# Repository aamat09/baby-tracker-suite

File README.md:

# Baby Tracker Suite

A baby care tracking system built on Home Assistant, n8n, PostgreSQL, and ESP32. Born out of a contraction tracker built for labor, evolved into a full newborn care dashboard once my son arrived plus a ~$10 3D-printed physical remote for those 3am diaper-change logs.

## Features

- **One-tap logging** of feeds, diapers, sleep, baths, medicine, tummy time, weight, pumping, and notes. 17 event types across 8 categories
- **Multi-channel fan-out** on every press: PostgreSQL, both phones, Echo Show, and Discord via a single n8n webhook
- **Live HA dashboard** with daily stats (feeds/diapers today, sleep total, last feed/diaper) polled every 30s
- **3D-printed physical remote** ESP32-C3 + a 15-button 4x4 matrix + WS2812 feedback LED, MQTT over WiFi
- **Reproducible PCB**  fully-routed 2-layer KiCad board *and* a 3D-printed copper-tape groove board, both generated from script
- **2-hour pump reminders** with independent per-side timers
- **Retired contraction tracker**  the labor-day origin story, Ring panic button + on-demand Ollama labor-stage AI assessment

## The Story

When my wife went into labor, we needed a way to log contractions without fumbling with phone apps. We paired a Ring Alarm Panic Button (Z-Wave) to our home automation stack where one press logged the contraction, timestamped it in PostgreSQL, notified both phones, posted to Discord, and announced it on the Echo Show. It worked beautifully for 700+ contractions over two weeks.

When we got to the hospital, the Ring button was back home. So we added intensity-coded buttons (Mild/Moderate/Strong/Intense) to the HA dashboard with color coding, stats (average gap, frequency), and an on-demand AI assessment powered by Ollama that would estimate the labor stage.

My son was born the next day. The contraction tracker was retired the same day and replaced with a baby tracker covering feeds, diapers, sleep, baths, medicine, tummy time, weight, pumping, and notes.

Keeping the same low-friction (high-WAF) style, we then built a 3D-printed physical remote with labeled buttons so nobody has to unlock a phone to log a diaper change at 3am.

## Architecture

```
Physical Button / HA App / Siri Shortcut
        |
        v
   n8n Webhook (POST /webhook/baby-event)
        |
   +----+----+----+----+
   |    |    |    |    |
   v    v    v    v    v
  DB  Phone Phone Echo Discord
  PG   you   ptnr Show
        |
        v
   n8n Log API (GET /webhook/baby-log)
        |
        v
   HA REST Sensor (polls every 30s)
        |
        v
   HA Dashboard (stats + journal + buttons)
```

## Components

### Contraction Tracker (retired)

The original. Ring Panic Button press -> Z-Wave JS UI -> Python bridge -> MQTT + n8n webhook -> full pipeline.

| File | Description |
|------|-------------|
| `contraction-tracker/zwave_panic_mqtt.py` | Python bridge: Z-Wave WebSocket -> MQTT + webhook |
| `contraction-tracker/n8n/contraction_tracker.json` | Main workflow: webhook -> Discord, DB, notifications |
| `contraction-tracker/n8n/contraction_note_logger.json` | MQTT-triggered note logger |
| `contraction-tracker/n8n/contraction_log_api.json` | GET API: returns entries + 2-hour stats |
| `contraction-tracker/n8n/contraction_ai_assessment.json` | On-demand Ollama AI labor stage assessment |
| `contraction-tracker/ha/dashboard.json` | HA Lovelace dashboard (intensity buttons, journal, AI) |
| `contraction-tracker/ha/configuration_snippets.yaml` | HA config: rest_command, input_text, REST sensor |

Features added during labor:
- 4 color-coded intensity buttons (Mild/Moderate/Strong/Intense)
- Real-time stats: contraction count, average gap, average intensity (last 2 hours)
- On-demand AI assessment via Ollama (gpt-oss model) with timestamp
- Press feedback: haptic vibration + button scale animation
- iPhone home screen shortcut via Apple Shortcuts deep link

### Baby Tracker (active)

Full newborn care tracker. 17 event types across 8 categories.

| File | Description |
|------|-------------|
| `baby-tracker/n8n/baby_event_logger.json` | Main workflow: webhook -> DB + phone notifications |
| `baby-tracker/n8n/baby_note_logger.json` | MQTT-triggered note logger |
| `baby-tracker/n8n/baby_log_api.json` | GET API: returns entries + daily stats |
| `baby-tracker/n8n/pump_reminder.json` | 2-hour pump reminder (independent timers per pump) |
| `baby-tracker/ha/dashboard.json` | HA Lovelace dashboard |
| `baby-tracker/ha/configuration_snippets.yaml` | HA config snippets |

Event types:
- **Feed:** breast, bottle, solid
- **Pump:** left, right (with 2h reminder)
- **Diaper:** pee, poop, both, change
- **Other:** sleep (toggle), bath, medicine, tummy_time, weight
- **Notes:** regular, special (star-prefixed)

Stats tracked: last feed time/type, last diaper time/type, feeds today, diapers today, sleep total today, baths/medicines/tummy times/pumps today.

### Baby Tracker App — Home Assistant add-on (separate repo)

A **single-container Home Assistant app** that bundles everything above with
**no n8n and no external database**: an Ingress web UI (the colorful button
dashboard), local SQLite storage, the same stats/journal, pump reminders, and
native HA entities via MQTT discovery — and it still listens to the ESP32
remote. It lives in its own installable repo:

➡️ **[hms-homelab/hms-baby-tracker](https://github.com/hms-homelab/hms-baby-tracker)**
(FastAPI + SQLite; add the repo URL under Settings → Add-ons/Apps → Repositories).

<p align="center"><em>The add-on's Ingress web UI (left) and its Home Assistant app page (right) — runs as a native HA add-on, no n8n or external DB.</em></p>

The n8n + PostgreSQL path in this repo remains as the advanced/legacy backend;
the app is the portable, one-click way to run the whole thing.

### Baby Remote (in progress)

3D-printed physical remote control with ESP32-C3, 15 tactile buttons, RGB LED feedback, and a 0.96" OLED status screen.

<p align="center"><em>The remote with its 0.96" OLED — last feed, last pump and the next-pump reminder, pushed live over MQTT by n8n.</em></p>

> **🎛️ Want one without building it?** The remote is made in small batches —
> **[join the device waitlist →](https://www.shmaestro.com/waitlist)**.

| File | Description |
|------|-------------|
| `baby-remote/kicad/` | 2-layer PCB (DRC-clean, Freerouting-routed) — the manufactured board |
| `baby-remote/kicad/fab/baby-remote-jlcpcb.zip` | Gerbers + drill, ready to upload to JLCPCB |
| `baby-remote/scad/baby-remote-pcb.scad` | OpenSCAD 3D-printed PCB substrate (grooved board = device back; bottom feet) |
| `baby-remote/scad/baby-remote-pcb-case.scad` | OpenSCAD snap-fit cap (walls + ledge + barrels + labels); board snaps in |
| `baby-remote/scad/button_plunger.stl` | Button plunger (print 15×) |
| `baby-remote/scad/led_window.stl` | LED window (print 1× in clear filament) |
| `baby-remote/esphome/baby_remote.yaml` | ESPHome firmware: matrix -> MQTT -> n8n / the app |

See [Hardware](#hardware) for the button layout, matrix wiring, PCB, and BOM.

### Database

| File | Description |
|------|-------------|
| `db/schema.sql` | PostgreSQL schema for both tables |

Both tables live in the `maestro_hub` database on PostgreSQL 17 at homelab.local.

## Hardware

The **Baby Remote** is a 3D-printed, battery-powered ESP32-C3 keypad. 15 tactile
switches on a diodeless **4x4 scan matrix** (16th cell is the LED window), each
press published over MQTT to the same n8n webhook the app and Siri use.

Button layout (4x4 grid, last cell = RGB LED):
```
 Breast  | Bottle  |  Solid  |  Sleep
 Pump L  | Pump R  |  Bath   |  Meds
  Pee    |  Poop   |  Both   | Change
 Tummy   | Weight  |  Note   |  [LED]
```

Matrix -> GPIO (firmware `baby-remote/esphome/baby_remote.yaml` == PCB):

| Signal | GPIO | Net |
|---|---|---|
| Rows (drive) | GPIO0, GPIO1, GPIO3, GPIO4 | `ROW0..3` |
| Columns (sense) | GPIO5, GPIO6, GPIO7, GPIO10 | `COL0..3` |
| WS2812B LED | GPIO8 | `LED_DIN` |

PCB -- two interchangeable designs, both script-generated and reproducible:
- **KiCad** (`baby-remote/kicad/`)  fully-routed **2-layer** board (rows on
  F.Cu, columns on B.Cu), DRC clean (0 violations / 0 unconnected / 0 parity),
  Freerouting-routed, JLCPCB-ready. Regenerate with `gen_schematic.py` ->
  `pcbgen.py`; route via Specctra DSN/SES.
- **OpenSCAD groove board** (`baby-remote/scad/baby-remote-pcb.scad`)  3D-printed
  substrate with copper-tape/tinned-wire grooves; rows on the top face, columns
  on the bottom, switch legs bridging faces (crossing-free).

BOM (~$10):

| Part | Qty |
|---|---|
| ESP32-C3 SuperMini | 1 |
| TP4056 USB-C LiPo charger | 1 |
| 3.7V LiPo 500mAh | 1 |
| 6x6x5mm tactile switches | 15 |
| WS2812B RGB LED | 1 |
| Slide switch (power) | 1 |

## Infrastructure

- **Home Assistant:** KVM/VM at homeassistant.local (dashboards, scripts, REST sensors)
- **n8n:** Native at homelab.local:5678 (workflow automation, webhooks)
- **PostgreSQL 17:** Native at homelab.local:5432 (data storage)
- **EMQX:** Native at homelab.local:1883 (MQTT broker)
- **Ollama:** ollama.local:11434 (AI assessment, RTX 3050)
- **ESPHome:** For ESP32 device firmware

## Install as a Home Assistant App

The fastest path — no n8n, no PostgreSQL, no manual scripts:

1. **Settings → Add-ons → Add-on Store** (shown as **Apps** on HA 2026.2+) →
   ⋮ → **Repositories** → add `https://github.com/hms-homelab/hms-baby-tracker`.
2. Install **Baby Tracker**, then **Start** it.
3. Open the **Web UI** (Ingress) — the button dashboard is right there.
4. *(optional)* In the app's **Configuration** tab set `notify_targets`
   (e.g. `mobile_app_your_phone`) to get press + pump-reminder notifications,
   and adjust `timezone` / `pump_hours`.

It auto-connects to the HA Mosquitto broker, so the **ESP32 remote keeps
working** (publishes to `baby/remote/event`) and native HA sensors/buttons
appear automatically via MQTT discovery. Data lives in the add-on's `/data`
(SQLite). Full reference:
[hms-baby-tracker DOCS](https://github.com/hms-homelab/hms-baby-tracker/blob/main/baby_tracker/DOCS.md).

## Quick Start (advanced / legacy n8n backend)

### 1. Database

```bash
psql -d maestro_hub -f db/schema.sql
```

### 2. n8n + Home Assistant

```bash
# Import the n8n workflows (n8n UI or API)
#   baby-tracker/n8n/*.json
# Add the HA snippets to configuration.yaml
#   baby-tracker/ha/configuration_snippets.yaml
# Import the dashboard into HA storage (.storage/lovelace.<name>)
#   baby-tracker/ha/dashboard.json
# Create the HA scripts referenced by the dashboard (rest_command + input_text,
#   see baby-tracker/ha/configuration_snippets.yaml)
```

### 3. Flash the remote

```bash
esphome run baby-remote/esphome/baby_remote.yaml
```

### 4. Build the remote

Print the case parts (`baby-remote/scad/*.stl`), fabricate the PCB
(KiCad Gerbers or the OpenSCAD groove board), and assemble.

## Related Projects

Part of the [Smart Home Maestro](https://github.com/hms-homelab) homelab:
- [hms-cpap](https://github.com/hms-homelab/hms-cpap) multi platform service for realtime visualization of sleep based data on cpap. 
- [hms-claude-mem](https://github.com/hms-homelab/hms-claude-mem) -- semantic memory MCP server (Redis vectorsets + Ollama)
- [hms-mm](https://github.com/hms-homelab/hms-mm) -- dual ESP32-C3 WiFi SD-card bridge
- [hms-scale-esp](https://github.com/hms-homelab/hms-scale-esp) -- ESP32-C3 BLE scale gateway

## License

MIT License -- see [LICENSE](LICENSE) for details.

## Support

If this project is useful to you, consider buying me a coffee!

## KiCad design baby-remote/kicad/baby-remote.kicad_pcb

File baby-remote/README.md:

# Baby Remote — 3D-printed physical buttons for the baby tracker

A handheld 15-button remote so you can log a feed/diaper/sleep with one press
instead of unlocking a phone at 3am. An ESP32-C3 reads the buttons and publishes
each press over MQTT; Home Assistant / n8n pick it up and log the event.

> "She wanted physical buttons instead of the classic yaml." — and here we are.

## How it works

```
[15 tactile buttons] --GPIO--> ESP32-C3 --WiFi/MQTT--> broker --> Home Assistant / n8n --> PostgreSQL
                                  |
                                  +-- WS2812B LED flashes the button's colour as confirmation
```

Each button publishes to `baby/remote/event` with a small JSON payload
(`{"event_type":"feed","event_subtype":"breast"}`). The onboard RGB LED blinks
the event's colour so you get tactile *and* visual confirmation.

## Bill of materials

| Qty | Part | Notes |
|-----|------|-------|
| 1 | ESP32-C3 SuperMini | any C3 dev board with exposed GPIOs |
| 1 | TP4056 USB-C charging board | LiPo charge + protection |
| 1 | 3.7V LiPo, 500–800 mAh | ~48×30×5 mm fits the bay |
| 15 | 6×6×5 mm tactile push buttons | through-hole, 4-pin |
| 1 | WS2812B RGB LED | feedback indicator |
| — | hookup wire, solder | shared GND bus + 15 signal wires |

## Print

Two-part **snap-fit** design (no separate tray). OpenSCAD sources + exported STLs
in `scad/`:

| Source | STL | Qty | Orientation |
|--------|-----|-----|-------------|
| [`baby-remote-pcb.scad`](scad/baby-remote-pcb.scad) | `baby-remote-pcb.stl` | 1 | grooves up (printed PCB substrate / device back) |
| [`baby-remote-pcb-case.scad`](scad/baby-remote-pcb-case.scad) | `baby-remote-pcb-case.stl` | 1 | top-face down (barrels point up) |
| — | `button_plunger.stl` | **15** | nub up / skirt-opening down — no supports |
| — | `led_window.stl` | 1 | clear/translucent filament |

The populated board **snaps up into the cap** from below: an internal ledge stops
it (top face up) and snap ridges catch its bottom edge. The board *is* the back of
the device — bottom feet lift the exposed wire side off the surface (a snap-on back
cover is a v2). The buttons are a **plunger-in-barrel** design: each plunger drops
into a barrel molded into the cap, rests on its tactile switch, and is captured by
the cap — no glue, won't fall out or spin. Tune `plunger_clear` / `hole_clear` (and
`pcb_clear` for the board fit) in the SCAD if your printer runs tight/loose.

## Wiring

Every switch: one leg → its GPIO (`INPUT_PULLUP`, active-low), the other leg →
a shared **GND bus**. WS2812B data → **GPIO8**.

| Row | Buttons (GPIO) |
|-----|----------------|
| 0 | Breast `0`, Bottle `1`, Solid `2`, Sleep `3` |
| 1 | Pump L `4`, Pump R `5`, Bath `6`, Meds `7` |
| 2 | Pee `9`, Poop `10`, Both `18`, Change `19` |
| 3 | Tummy `20`, Weight `21`, Note `22` |

> **Note:** the firmware also samples battery voltage on an ADC pin. On the C3
> SuperMini the usable ADC pins overlap the button GPIOs — pick a free ADC-capable
> pin for the divider (or drop battery monitoring) so it doesn't clash with a button.

## Flash

```bash
cd esphome
cp secrets.yaml.example secrets.yaml   # fill in WiFi + MQTT
esphome run baby_remote.yaml
```

Firmware: [`esphome/baby_remote.yaml`](esphome/baby_remote.yaml). It connects to
WiFi + MQTT, defines a `binary_sensor` per button, and on press runs a script that
flashes the LED in the button's colour and publishes the event.

## Integrate

Point it at any MQTT broker Home Assistant or n8n listens on. The matching
HA config + n8n event-logger flow live one level up in
[`../baby-tracker/`](../baby-tracker/) (`ha/configuration_snippets.yaml`,
`n8n/baby_event_logger.json`). Subscribe to `baby/remote/event` and route each
`event_type`/`event_subtype` to your logger of choice.

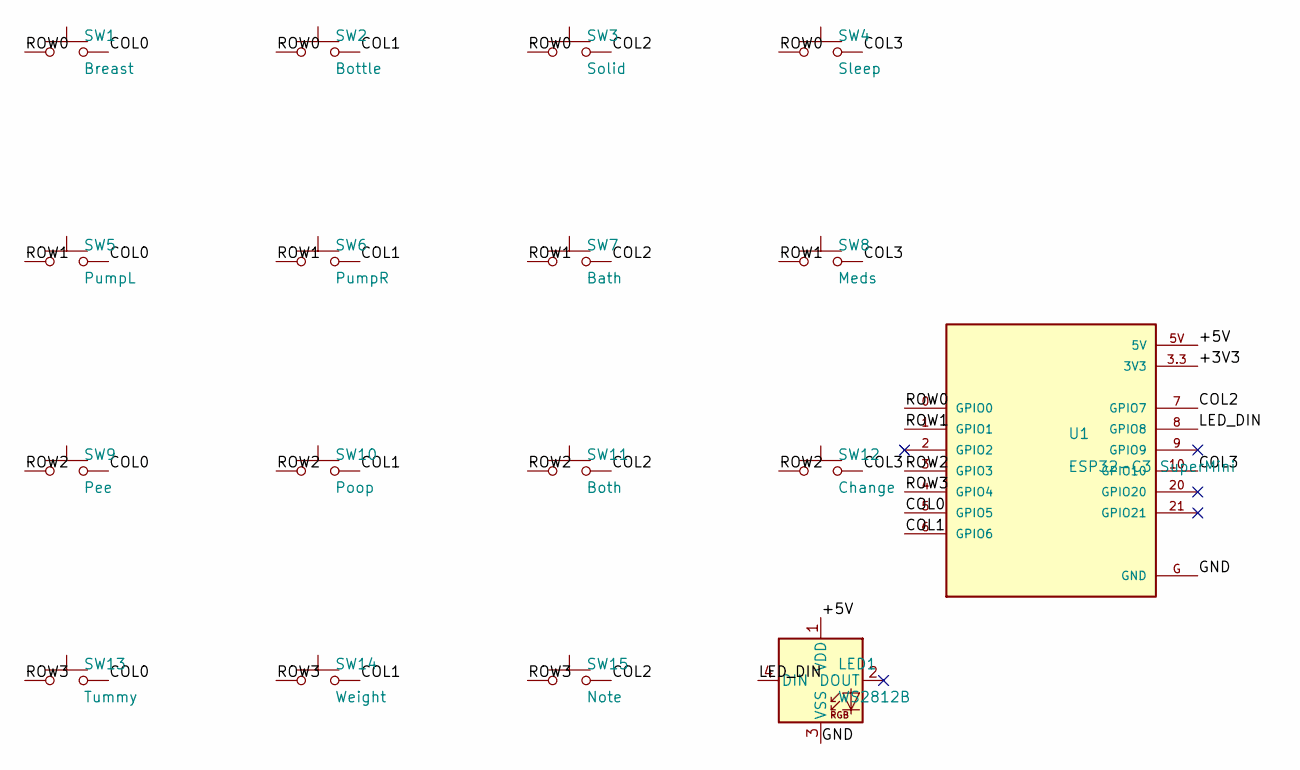
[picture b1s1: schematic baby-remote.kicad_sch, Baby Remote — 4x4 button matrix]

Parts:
LED1: WS2812B; LED_WS2812B_PLCC4_5.0x5.0mm_P3.2mm
SW1: Breast; SW_PUSH_6mm_H13mm
SW2: Bottle; SW_PUSH_6mm_H13mm
SW3: Solid; SW_PUSH_6mm_H13mm
SW4: Sleep; SW_PUSH_6mm_H13mm
SW5: PumpL; SW_PUSH_6mm_H13mm
SW6: PumpR; SW_PUSH_6mm_H13mm
SW7: Bath; SW_PUSH_6mm_H13mm
SW8: Meds; SW_PUSH_6mm_H13mm
SW9: Pee; SW_PUSH_6mm_H13mm
SW10: Poop; SW_PUSH_6mm_H13mm
SW11: Both; SW_PUSH_6mm_H13mm
SW12: Change; SW_PUSH_6mm_H13mm
SW13: Tummy; SW_PUSH_6mm_H13mm
SW14: Weight; SW_PUSH_6mm_H13mm
SW15: Note; SW_PUSH_6mm_H13mm
U1: ESP32-C3 SuperMini; MODULE_ESP32-C3_SUPERMINI

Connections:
/+3V3: U1.3.3 (3V3)
/+5V: LED1.1 (VDD), U1.5V
/COL0: SW1.2, SW5.2, SW9.2, SW13.2, U1.5 (GPIO5)
/COL1: SW2.2, SW6.2, SW10.2, SW14.2, U1.6 (GPIO6)
/COL2: SW3.2, SW7.2, SW11.2, SW15.2, U1.7 (GPIO7)
/COL3: SW4.2, SW8.2, SW12.2, U1.10 (GPIO10)
/GND: LED1.3 (VSS), U1.G (GND)
/LED_DIN: LED1.4 (DIN), U1.8 (GPIO8)
/ROW0: SW1.1, SW2.1, SW3.1, SW4.1, U1.0 (GPIO0)
/ROW1: SW5.1, SW6.1, SW7.1, SW8.1, U1.1 (GPIO1)
/ROW2: SW9.1, SW10.1, SW11.1, SW12.1, U1.3 (GPIO3)
/ROW3: SW13.1, SW14.1, SW15.1, U1.4 (GPIO4)

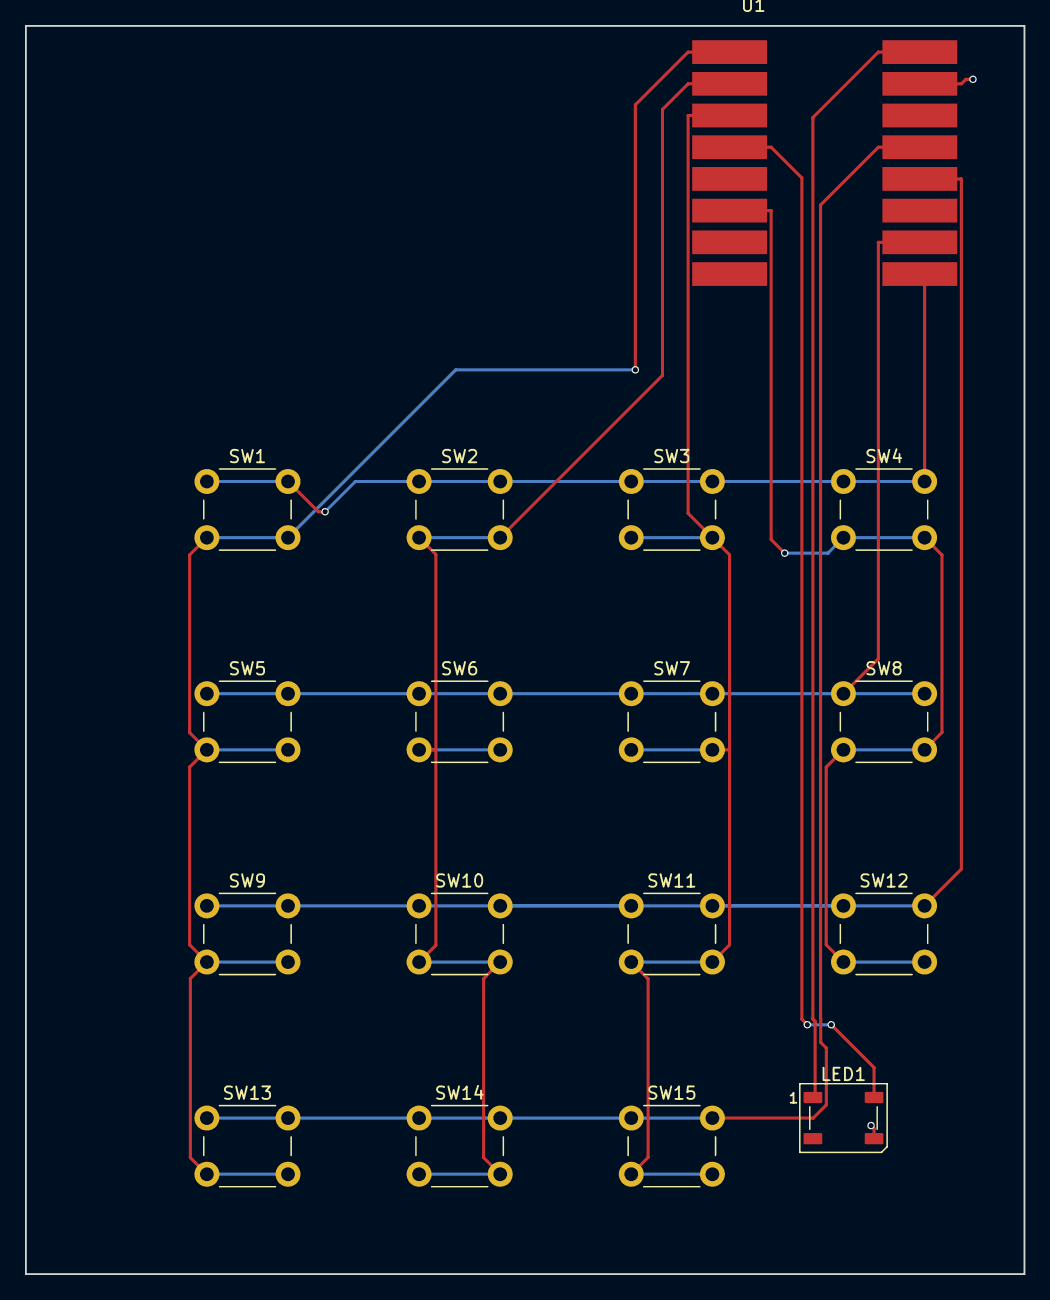
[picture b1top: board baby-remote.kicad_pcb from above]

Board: 2 copper layers, 80.0 x 100.0 mm, 17 parts (0 on the bottom side), 11 nets.

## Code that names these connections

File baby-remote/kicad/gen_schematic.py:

#!/usr/bin/env python3
"""Generate baby-remote.kicad_sch: ESP32-C3 SuperMini + 4x4 button matrix.

Wiring (matches baby_remote.yaml matrix_keypad):
  Rows: GPIO0,1,3,4 -> ROW0..3 ; Cols: GPIO5,6,7,10 -> COL0..3 ; LED: GPIO8.
Connectivity is by net LABELS on pin endpoints (no wires); KiCad joins pins
that share a label name. Placement is snapped to the 1.27mm grid; unused
GPIOs get no-connect flags and power nets get PWR_FLAGs (clean ERC).
"""
import re, uuid, os

KICAD_SYM = "/Applications/KiCad/KiCad.app/Contents/SharedSupport/symbols"
HERE = os.path.dirname(os.path.abspath(__file__))
GRID = 1.27
def snap(v): return round(v / GRID) * GRID
def uid(): return str(uuid.uuid4())

def extract_symbol(lib_path, name):
    s = open(lib_path).read()
    i = s.find(f'(symbol "{name}"')
    if i < 0: raise SystemExit(f"symbol {name} not found in {lib_path}")
    depth = 0
    for j in range(i, len(s)):
        if s[j] == '(': depth += 1
        elif s[j] == ')':
            depth -= 1
            if depth == 0: return s[i:j+1]
    raise SystemExit("unbalanced")

def pins(block):
    out = []
    for m in re.finditer(
        r'\(pin\s+\S+\s+\S+\s+\(at\s+([-\d.]+)\s+([-\d.]+)\s+([-\d.]+)\)'
        r'.*?\(name\s+"([^"]+)".*?\(number\s+"([^"]+)"', block, re.S):
        x, y, a, nm, num = m.groups()
        out.append((nm, num, float(x), float(y), float(a)))
    return out

c3_block  = extract_symbol(f"{HERE}/ESP32-C3_SUPERMINI.kicad_sym", "ESP32-C3_SUPERMINI")
sw_block  = extract_symbol(f"{KICAD_SYM}/Switch.kicad_sym", "SW_Push")
led_block = extract_symbol(f"{KICAD_SYM}/LED.kicad_sym", "WS2812B")

c3_pins, sw_pins, led_pins = pins(c3_block), pins(sw_block), pins(led_block)

c3_libid  = "ESP32-C3-SuperMini:ESP32-C3_SUPERMINI"
sw_libid  = "Switch:SW_Push"
led_libid = "LED:WS2812B"
c3_block_p  = c3_block.replace('(symbol "ESP32-C3_SUPERMINI"', f'(symbol "{c3_libid}"', 1)
sw_block_p  = sw_block.replace('(symbol "SW_Push"', f'(symbol "{sw_libid}"', 1)
led_block_p = led_block.replace('(symbol "WS2812B"', f'(symbol "{led_libid}"', 1)

ROOT = uid()
parts, labels, ncs, SYMS = [], [], [], {}

def place_label(net, x, y, ang=0):
    labels.append(f'  (label "{net}" (at {x:.2f} {y:.2f} {ang}) '
                  f'(effects (font (size 1.27 1.27)) (justify left bottom)) (uuid "{uid()}"))')

def no_connect(x, y):
    ncs.append(f'  (no_connect (at {x:.2f} {y:.2f}) (uuid "{uid()}"))')

def place_symbol(libid, ref, val, x, y, pinlist, footprint=""):
    x, y = snap(x), snap(y)
    sym_uuid = uid(); SYMS[ref] = sym_uuid
    pin_uuids = "\n".join(f'    (pin "{num}" (uuid "{uid()}"))' for (_, num, *_) in pinlist)
    fp = (f'    (property "Footprint" "{footprint}" (at {x} {y} 0) '
          f'(effects (font (size 1.27 1.27)) hide))') if footprint else ""
    parts.append(f'''  (symbol (lib_id "{libid}") (at {x} {y} 0) (unit 1)
    (exclude_from_sim no) (in_bom yes) (on_board yes) (dnp no)
    (uuid "{sym_uuid}")
    (property "Reference" "{ref}" (at {x+2} {y-2} 0) (effects (font (size 1.27 1.27)) (justify left)))
    (property "Value" "{val}" (at {x+2} {y+2} 0) (effects (font (size 1.27 1.27)) (justify left)))
{fp}
{pin_uuids}
    (instances (project "baby-remote" (path "/{ROOT}" (reference "{ref}") (unit 1))))
  )''')
    return {nm: (x + px, y - py) for (nm, num, px, py, pa) in pinlist}, \
           {num: (x + px, y - py) for (nm, num, px, py, pa) in pinlist}

# ---- C3 module ----
c3_byname, _ = place_symbol(c3_libid, "U1", "ESP32-C3 SuperMini", 180.34, 109.22, c3_pins,
                            "ESP32-C3-SuperMini:MODULE_ESP32-C3_SUPERMINI")
gpio_net = {"GPIO0":"ROW0","GPIO1":"ROW1","GPIO3":"ROW2","GPIO4":"ROW3",
            "GPIO5":"COL0","GPIO6":"COL1","GPIO7":"COL2","GPIO10":"COL3",
            "GPIO8":"LED_DIN","3V3":"+3V3","5V":"+5V","GND":"GND"}
for nm, (px, py) in c3_byname.items():
    if nm in gpio_net:
        place_label(gpio_net[nm], px, py)
    elif nm in ("GPIO2", "GPIO9", "GPIO20", "GPIO21"):
        no_connect(px, py)


# ---- 4x4 switch matrix (skip (3,3) = LED window -> WS2812) ----
LABELS = [["Breast","Bottle","Solid","Sleep"],
          ["PumpL","PumpR","Bath","Meds"],
          ["Pee","Poop","Both","Change"],
          ["Tummy","Weight","Note","LED"]]
x0, y0, dx, dy = 60.96, 60.96, 30.48, 25.40
n = 1
for r in range(4):
    for c in range(4):
        sx, sy = x0 + c*dx, y0 + r*dy
        if r == 3 and c == 3:
            _, byn = place_symbol(led_libid, "LED1", "WS2812B", sx, sy, led_pins,
                                  "LED_SMD:LED_WS2812B_PLCC4_5.0x5.0mm_P3.2mm")
            if "1" in byn: place_label("+5V",     *byn["1"])
            if "3" in byn: place_label("GND",     *byn["3"])
            if "4" in byn: place_label("LED_DIN", *byn["4"])
            if "2" in byn: no_connect(*byn["2"])
            continue
        _, byn = place_symbol(sw_libid, f"SW{n}", LABELS[r][c], sx, sy, sw_pins, "Button_Switch_THT:SW_PUSH_6mm_H13mm")
        if "1" in byn: place_label(f"ROW{r}", *byn["1"])
        if "2" in byn: place_label(f"COL{c}", *byn["2"])
        n += 1

sch = f'''(kicad_sch
  (version 20250114)
  (generator "baby_remote_gen")
  (generator_version "9.0")
  (uuid "{ROOT}")
  (paper "A4")
  (title_block (title "Baby Remote — 4x4 button matrix") (rev "2026.1.0") (company "Smart Home Maestro"))
  (lib_symbols
{c3_block_p}
{sw_block_p}
{led_block_p}
  )
{chr(10).join(parts)}
{chr(10).join(labels)}
{chr(10).join(ncs)}
  (sheet_instances
    (path "/" (page "1"))
  )
)
'''
open(f"{HERE}/baby-remote.kicad_sch", "w").write(sch)
import json
json.dump({"root": ROOT, "refs": SYMS}, open(f"{HERE}/symbols.json","w"))
print(f"wrote: {len(parts)} symbols, {len(labels)} labels, {len(ncs)} no-connects")
